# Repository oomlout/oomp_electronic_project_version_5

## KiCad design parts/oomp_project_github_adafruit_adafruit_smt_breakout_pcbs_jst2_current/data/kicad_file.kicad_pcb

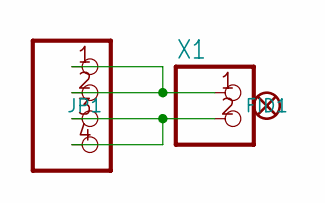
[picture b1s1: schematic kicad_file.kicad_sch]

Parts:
FID1: FIDUCIAL""; FIDUCIAL_1MM
JP1: PADS-4
X1: CON_JST_PH_2PIN; JSTPH2

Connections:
unnamed: JP1.1, JP1.2, X1.1
unnamed: JP1.3, JP1.4, X1.2

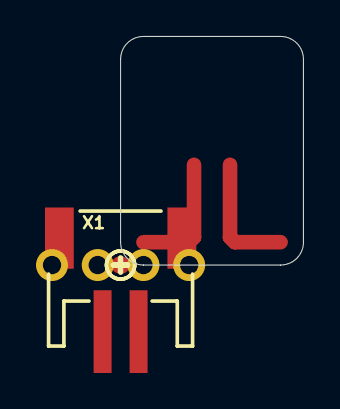
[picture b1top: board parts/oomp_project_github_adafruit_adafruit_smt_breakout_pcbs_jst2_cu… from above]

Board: 2 copper layers, 10.2 x 12.7 mm, 6 parts (1 on the bottom side), 2 nets.

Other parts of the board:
U$1: SYMBOL_PLUS
U$2: SYMBOL_MINUS
U$4: ADAFRUIT_3.5MM

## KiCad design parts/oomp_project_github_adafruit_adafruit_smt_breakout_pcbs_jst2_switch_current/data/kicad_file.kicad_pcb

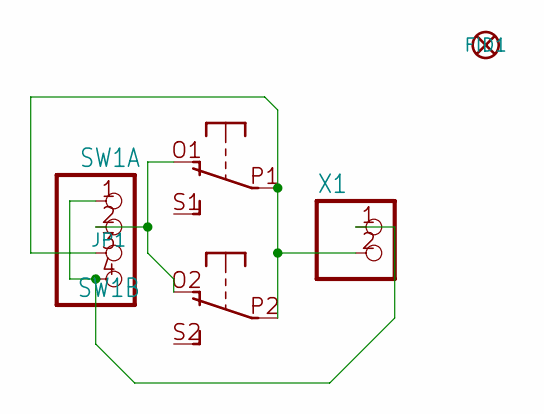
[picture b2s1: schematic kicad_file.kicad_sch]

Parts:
FID1: FIDUCIAL""; FIDUCIAL_1MM
JP1: PADS-4
SW1: DPDT-EG1390; EG1390
X1: CON_JST_PH_2PIN; JSTPH2

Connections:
GND: JP1.1, JP1.4, X1.1
unnamed: JP1.3, SW1.P1, SW1.P2, X1.2
unnamed: JP1.2, SW1.O1 (O), SW1.O2 (O)

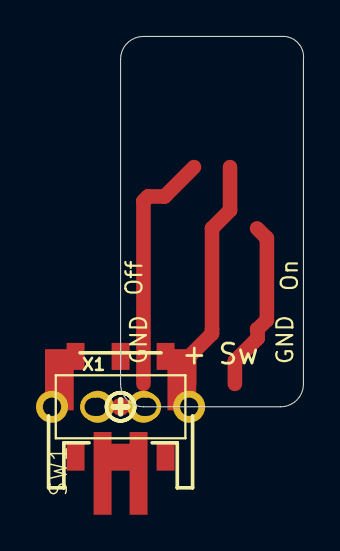
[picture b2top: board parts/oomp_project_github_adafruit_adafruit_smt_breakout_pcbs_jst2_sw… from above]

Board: 2 copper layers, 10.2 x 20.6 mm, 7 parts (1 on the bottom side), 3 nets.

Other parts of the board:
U$1: SYMBOL_PLUS
U$2: SYMBOL_MINUS
U$3: ADAFRUIT_5MM

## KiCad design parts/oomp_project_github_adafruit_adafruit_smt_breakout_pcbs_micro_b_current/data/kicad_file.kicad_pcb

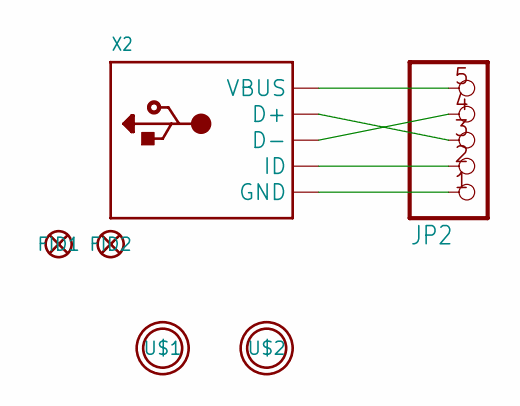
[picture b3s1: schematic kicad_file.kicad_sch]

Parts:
FID1, FID2: FIDUCIAL""; FIDUCIAL_1MM
JP2: HEADER-1X570MIL; 1X05_ROUND_70
U$1, U$2: MOUNTINGHOLE2.5; MOUNTINGHOLE_2.5_PLATED
X2: USBMICRO_20329; 4UCONN_20329

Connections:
D+: JP2.3, X2.D+
D-: JP2.4, X2.D-
GND: JP2.1, X2.BASE@1 (GND), X2.BASE@2 (GND), X2.GND, X2.SPRT@1 (GND), X2.SPRT@2 (GND), X2.SPRT@3 (GND), X2.SPRT@4 (GND)
ID: JP2.2, X2.ID
VBUS: JP2.5, X2.VBUS

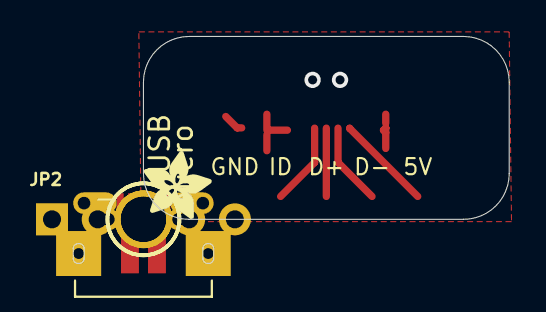
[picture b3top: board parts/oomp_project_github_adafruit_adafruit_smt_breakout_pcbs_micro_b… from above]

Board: 2 copper layers, 20.3 x 10.2 mm, 7 parts (0 on the bottom side), 5 nets.

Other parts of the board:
U$4: ADAFRUIT_3.5MM

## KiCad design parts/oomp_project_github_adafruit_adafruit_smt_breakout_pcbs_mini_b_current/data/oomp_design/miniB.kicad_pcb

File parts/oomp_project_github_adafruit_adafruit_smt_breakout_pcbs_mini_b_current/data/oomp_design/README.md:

# OOMP KiCad design copy

Open `miniB.kicad_pro` (or the `.kicad_pcb` / `.kicad_sch`) in KiCad. Local OOMP libraries are under `libraries/`. Original inputs are preserved in [../original/](../original/).

Only verified unchanged installed KiCad defaults were renamed. Modified, custom, unmatched and unavailable items remain unchanged. Soldering variants are never swapped during conversion. Existing pad coordinates, nets and UUIDs are preserved.

See [conversion_report.yaml](conversion_report.yaml) for every conversion and skip. Copy this directory before editing; regeneration refuses to overwrite edited design files.

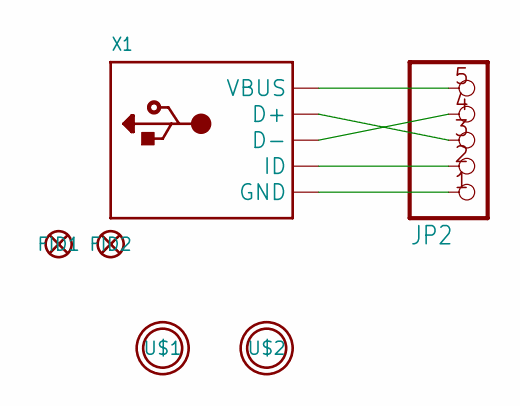
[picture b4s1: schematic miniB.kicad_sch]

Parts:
FID1, FID2: FIDUCIAL""; FIDUCIAL_1MM
JP2: HEADER-1X570MIL; 1X05_ROUND_70
U$1, U$2: MOUNTINGHOLE2.5; MOUNTINGHOLE_2.5_PLATED
X1: USBMINIBLARGE; USB-MINIB_LARGER

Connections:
D+: JP2.3, X1.D+
D-: JP2.4, X1.D-
GND: JP2.1, X1.GND, X1.GND1 (GND), X1.GND2 (GND), X1.GND3 (GND), X1.GND4 (GND)
ID: JP2.2, X1.ID
VBUS: JP2.5, X1.VBUS

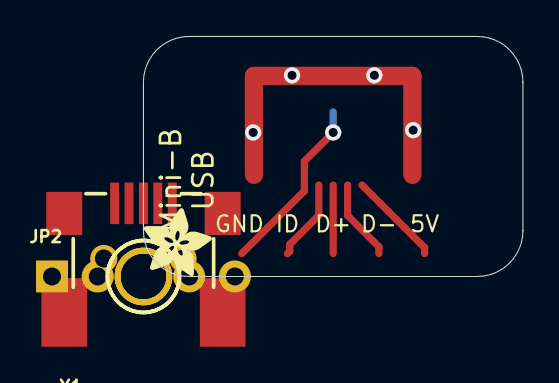
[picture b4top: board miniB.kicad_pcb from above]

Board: 2 copper layers, 21.1 x 13.3 mm, 7 parts (0 on the bottom side), 5 nets.

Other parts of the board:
U$4: ADAFRUIT_3.5MM
